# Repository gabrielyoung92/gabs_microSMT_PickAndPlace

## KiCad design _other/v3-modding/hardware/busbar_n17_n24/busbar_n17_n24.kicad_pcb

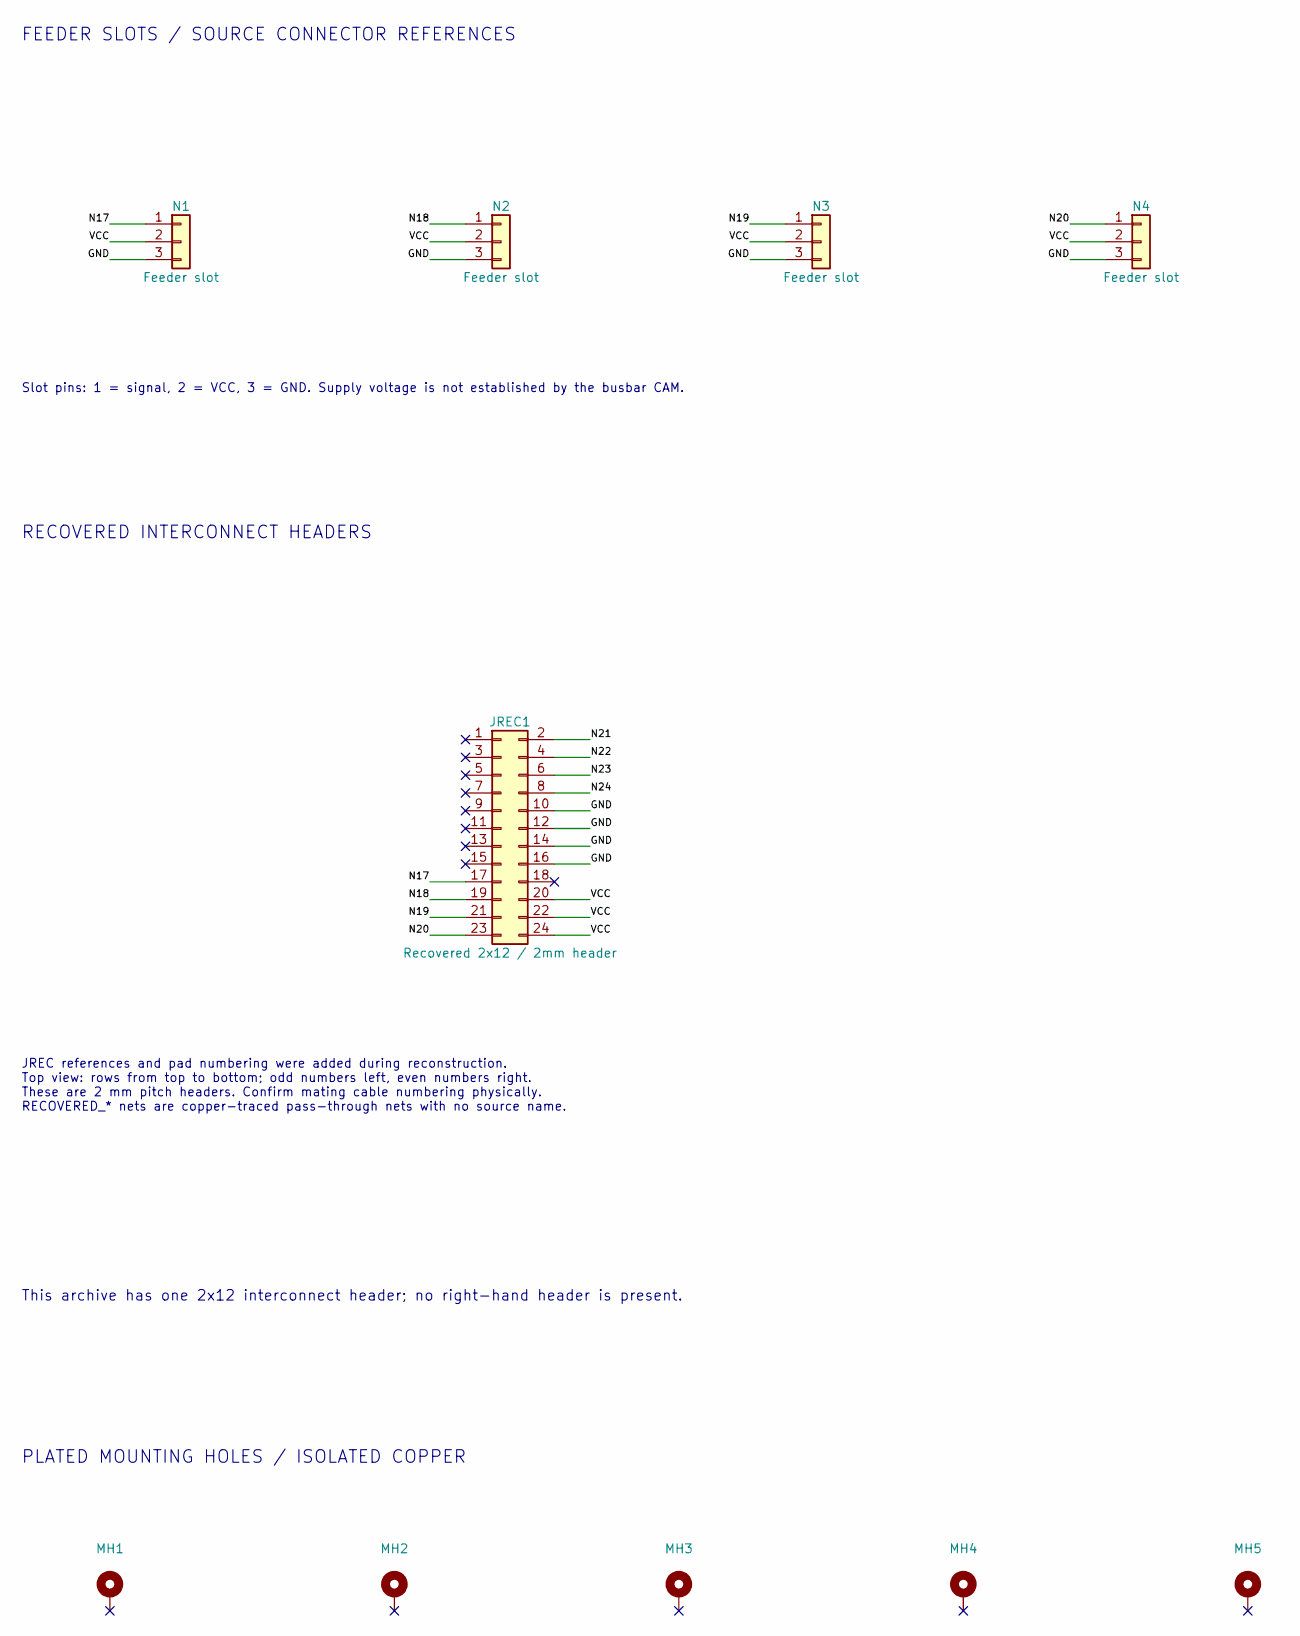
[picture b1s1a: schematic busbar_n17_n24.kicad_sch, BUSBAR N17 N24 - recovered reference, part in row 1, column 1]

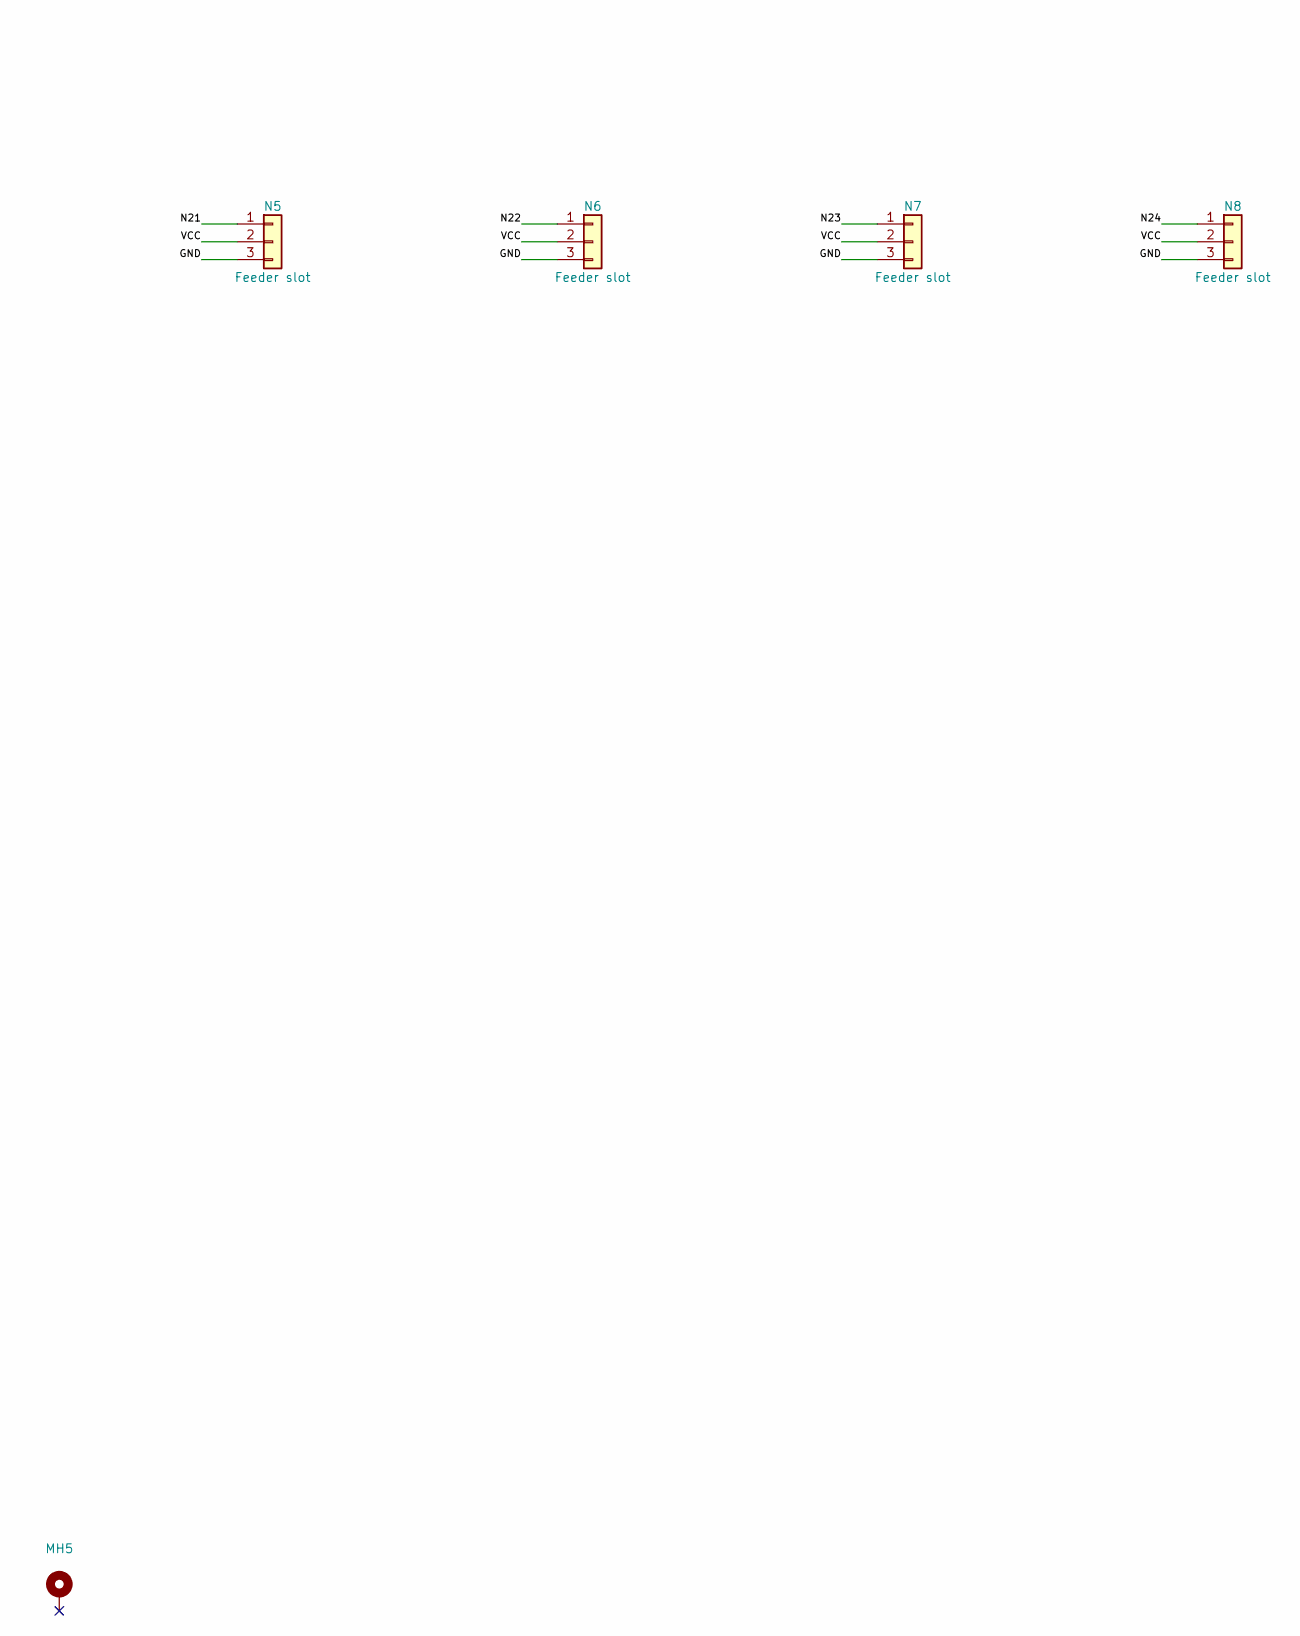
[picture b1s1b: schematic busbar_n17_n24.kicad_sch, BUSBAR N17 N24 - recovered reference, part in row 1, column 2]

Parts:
JREC1: Recovered 2x12 / 2mm header; PTH_24_357941b971
MH1, MH2, MH3, MH4, MH5: Plated mounting hole 3.3mm; PTH_1_508660c0b4
N1: Feeder slot; PTH_3_73baab2469
N2: Feeder slot; PTH_3_f185d45fd5
N3: Feeder slot; PTH_3_6d3198c4a7
N4: Feeder slot; PTH_3_f29aeb013d
N5: Feeder slot; PTH_3_40f9a56ae3
N6: Feeder slot; PTH_3_2e4f513424
N7: Feeder slot; PTH_3_8ca71f247a
N8: Feeder slot; PTH_3_1d444e7cb6

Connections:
/GND: JREC1.10, JREC1.12, JREC1.14, JREC1.16, N1.3, N2.3, N3.3, N4.3, N5.3, N6.3, N7.3, N8.3
/N17: JREC1.17, N1.1
/N18: JREC1.19, N2.1
/N19: JREC1.21, N3.1
/N20: JREC1.23, N4.1
/N21: JREC1.2, N5.1
/N22: JREC1.4, N6.1
/N23: JREC1.6, N7.1
/N24: JREC1.8, N8.1
/VCC: JREC1.20, JREC1.22, JREC1.24, N1.2, N2.2, N3.2, N4.2, N5.2, N6.2, N7.2, N8.2

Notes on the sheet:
FEEDER SLOTS / SOURCE CONNECTOR REFERENCES
Slot pins: 1 = signal, 2 = VCC, 3 = GND. Supply voltage is not established by the busbar CAM.
RECOVERED INTERCONNECT HEADERS
JREC references and pad numbering were added during reconstruction. Top view: rows from top to bottom; odd numbers left, even numbers right. These are 2 mm pitch headers. Confirm mating cable numbering physically. RECOVERED_* nets are copper-traced pass-through nets with no source name.
This archive has one 2x12 interconnect header; no right-hand header is present.
PLATED MOUNTING HOLES / ISOLATED COPPER

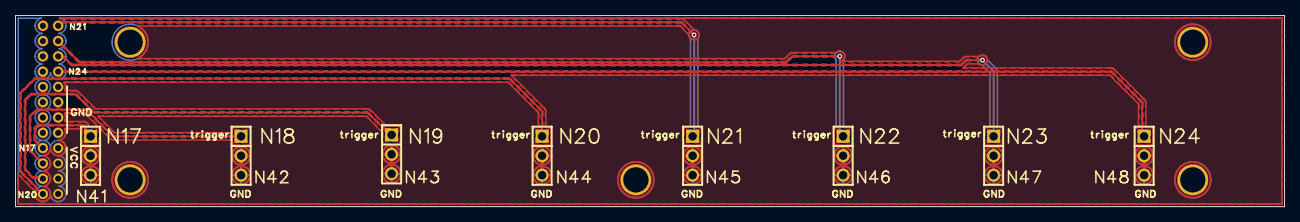
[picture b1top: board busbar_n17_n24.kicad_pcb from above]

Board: 2 copper layers, 166.0 x 25.0 mm, 14 parts (0 on the bottom side), 10 nets.

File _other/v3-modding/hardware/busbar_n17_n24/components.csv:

Reference,Value,Recovered footprint,Pad count,Inferred reference
N1,Feeder slot,MicroSMT_Recovered:PTH_3_73baab2469,3,False
N2,Feeder slot,MicroSMT_Recovered:PTH_3_f185d45fd5,3,False
N3,Feeder slot,MicroSMT_Recovered:PTH_3_6d3198c4a7,3,False
N4,Feeder slot,MicroSMT_Recovered:PTH_3_f29aeb013d,3,False
N5,Feeder slot,MicroSMT_Recovered:PTH_3_40f9a56ae3,3,False
N6,Feeder slot,MicroSMT_Recovered:PTH_3_2e4f513424,3,False
N7,Feeder slot,MicroSMT_Recovered:PTH_3_8ca71f247a,3,False
N8,Feeder slot,MicroSMT_Recovered:PTH_3_1d444e7cb6,3,False
JREC1,Recovered 2x12 / 2mm header,MicroSMT_Recovered:PTH_24_357941b971,24,True
MH1,Plated mounting hole 3.3mm,MicroSMT_Recovered:PTH_1_508660c0b4,1,True
MH2,Plated mounting hole 3.3mm,MicroSMT_Recovered:PTH_1_508660c0b4,1,True
MH3,Plated mounting hole 3.3mm,MicroSMT_Recovered:PTH_1_508660c0b4,1,True
MH4,Plated mounting hole 3.3mm,MicroSMT_Recovered:PTH_1_508660c0b4,1,True
MH5,Plated mounting hole 3.3mm,MicroSMT_Recovered:PTH_1_508660c0b4,1,True
